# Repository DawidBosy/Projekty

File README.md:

# Projekty
Projekty wykonywane w trakcie studiów

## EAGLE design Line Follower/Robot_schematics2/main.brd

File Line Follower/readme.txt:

Dawid Bosy
Projekt dotyczył przedmiotu Architektura Systemów Komputerowych - wykonywany był na 4 semestrze.
Celem było zbudowanie od podstaw robota, jeżdżącego po zaznaczonej na ziemi linii.

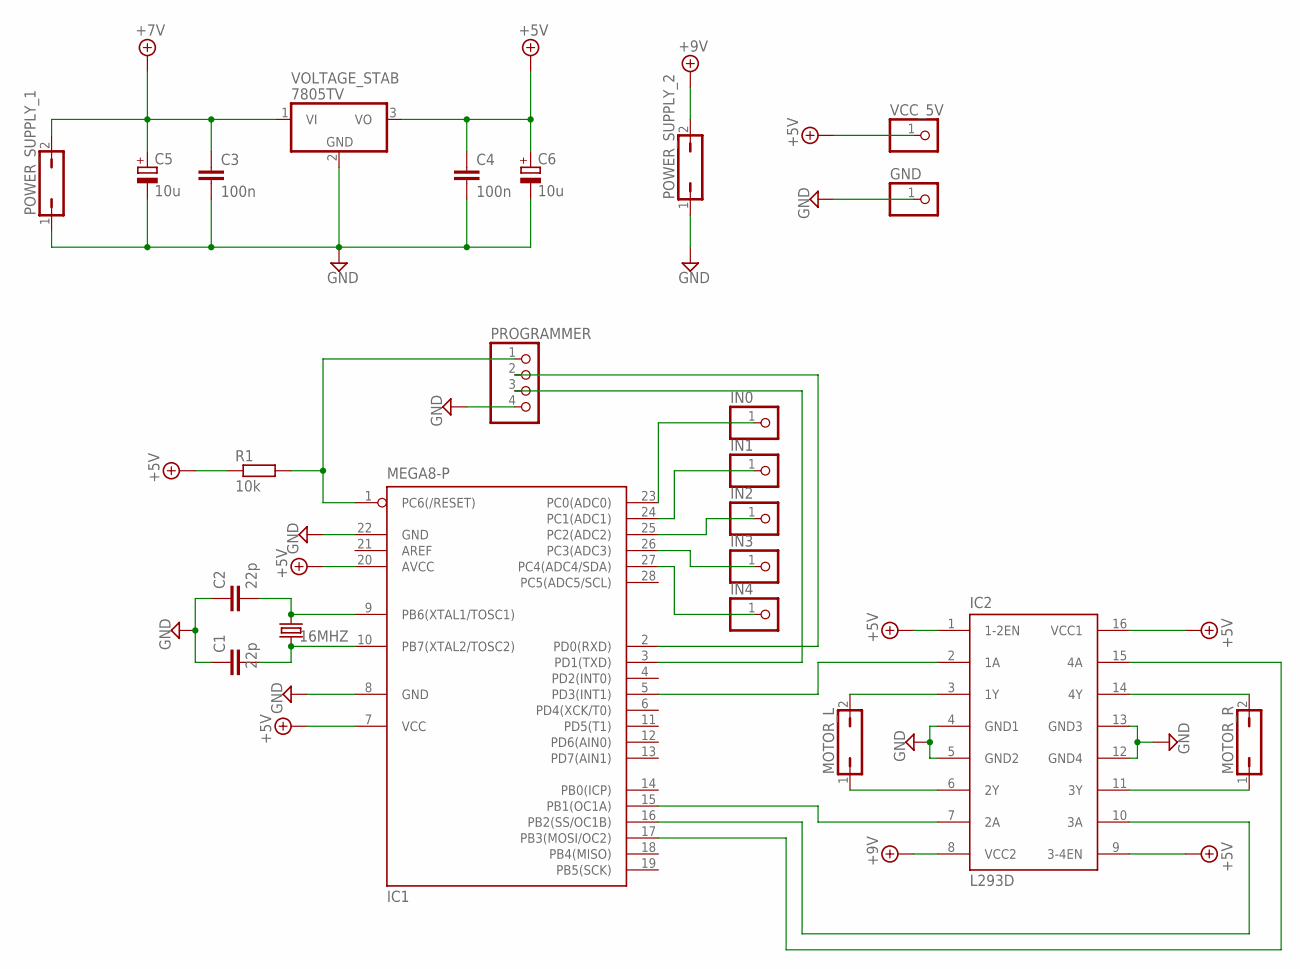
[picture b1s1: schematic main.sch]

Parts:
16MHZ: CRYSTALHC49S; HC49/S
C1, C2: 22p; C025-030X050
C3, C4: 100n; C025-030X050
C5, C6: 10u; E2,5-7
GND: PINHD-1X1; 1X01
IC1: MEGA8-P; DIL28-3
IC2: L293D; DIL16
IN0, IN1, IN2, IN3, IN4: PINHD-1X1; 1X01
MOTOR_L: JP1Q; JP1
MOTOR_R: JP1Q; JP1
POWER_SUPPLY_1, POWER_SUPPLY_2: JP1Q; JP1
PROGRAMMER: PINHD-1X4; 1X04
R1: 10k; 0204/5
VCC_5V: PINHD-1X1; 1X01
VOLTAGE_STAB: 7805TV; TO220V

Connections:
+5V: C4.1, C6.+, IC1.7 (VCC), IC1.20 (AVCC), IC2.1 (1-2EN), IC2.9 (3-4EN), IC2.16 (VCC1), R1.1, VCC_5V.1, VOLTAGE_STAB.3 (VO)
+7V: C3.1, C5.+, POWER_SUPPLY_1.2, VOLTAGE_STAB.1 (VI)
+9V: IC2.8 (VCC2), POWER_SUPPLY_2.2
GND: C1.1, C2.1, C3.2, C4.2, C5.-, C6.-, GND.1, IC1.8 (GND), IC1.22 (GND), IC2.4 (GND1), IC2.5 (GND2), IC2.12 (GND4), IC2.13 (GND3), POWER_SUPPLY_1.1, POWER_SUPPLY_2.1, PROGRAMMER.4, VOLTAGE_STAB.2 (GND)
MOTOR_L_1: IC1.5 (PD3(INT1)), IC2.2 (1A)
MOTOR_L_2: IC1.15 (PB1(OC1A)), IC2.7 (2A)
MOTOR_R2: IC1.17 (PB3(MOSI/OC2)), IC2.15 (4A)
MOTOR_R_1: IC1.16 (PB2(SS/OC1B)), IC2.10 (3A)
unnamed: IC2.11 (3Y), MOTOR_R.1
unnamed: IC2.14 (4Y), MOTOR_R.2
unnamed: IC2.3 (1Y), MOTOR_L.2
unnamed: IC2.6 (2Y), MOTOR_L.1
unnamed: 16MHZ.2, C2.2, IC1.9 (PB6(XTAL1/TOSC1))
unnamed: 16MHZ.1, C1.2, IC1.10 (PB7(XTAL2/TOSC2))
unnamed: IC1.23 (PC0(ADC0)), IN0.1
unnamed: IC1.24 (PC1(ADC1)), IN1.1
unnamed: IC1.25 (PC2(ADC2)), IN2.1
unnamed: IC1.27 (PC4(ADC4/SDA)), IN4.1
unnamed: IC1.26 (PC3(ADC3)), IN3.1
unnamed: IC1.3 (PD1(TXD)), PROGRAMMER.3
unnamed: IC1.2 (PD0(RXD)), PROGRAMMER.2
RESET: IC1.1 (PC6(/RESET)), PROGRAMMER.1, R1.2

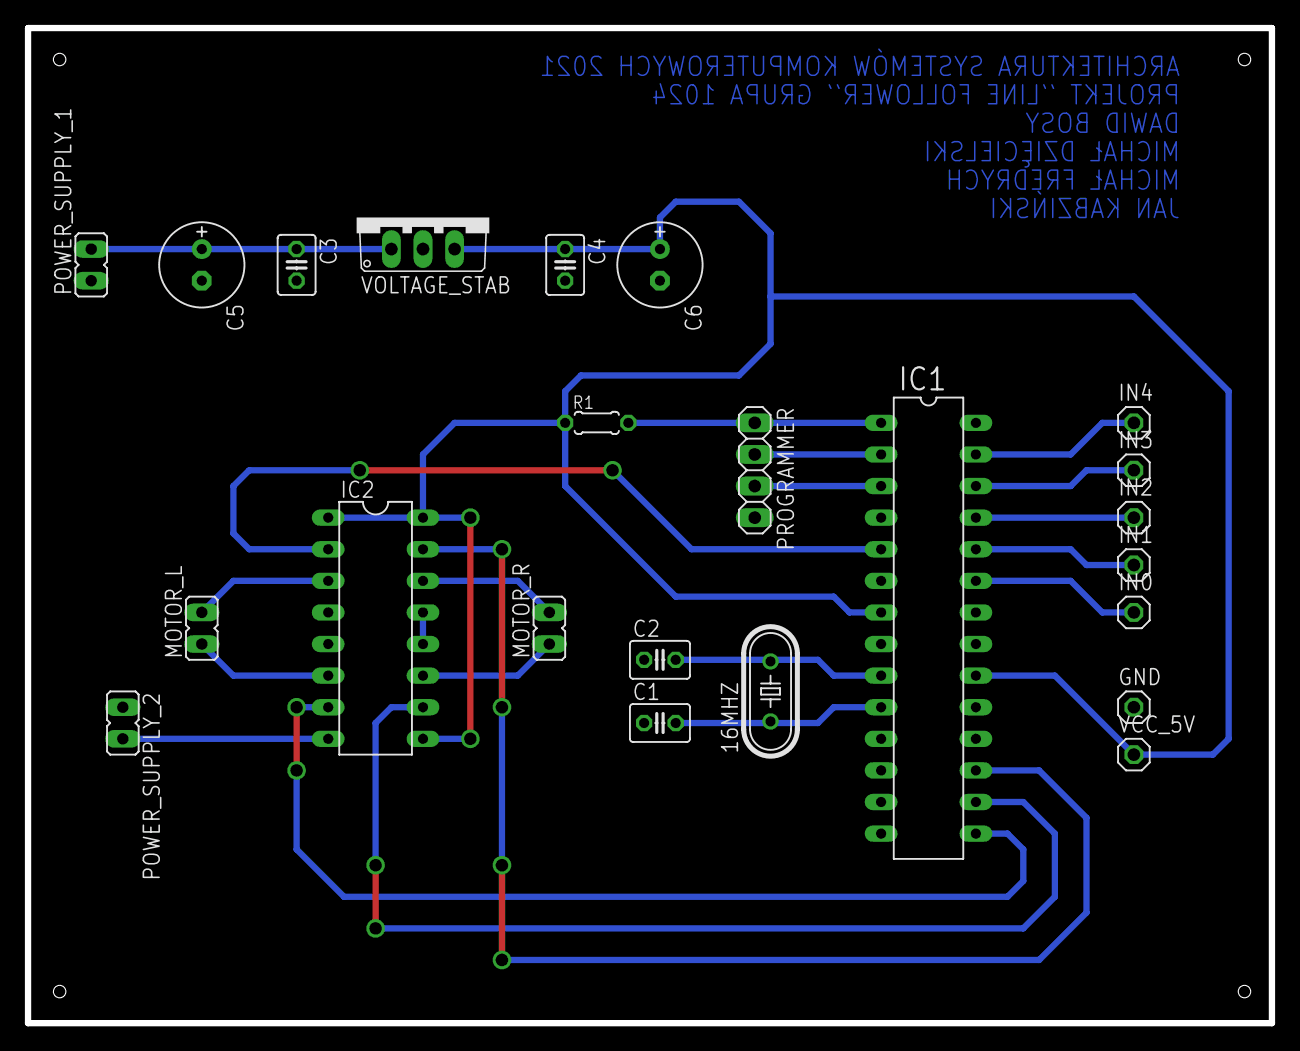
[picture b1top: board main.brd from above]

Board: 2 copper layers, 100.0 x 80.0 mm, 23 parts (0 on the bottom side), 22 nets.

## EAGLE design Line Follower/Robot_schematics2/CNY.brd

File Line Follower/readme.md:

# Robot Line Follower
Projekt dotyczył przedmiotu Architektura Systemów Komputerowych - wykonywany był na 4 semestrze.
Celem było zbudowanie od podstaw robota, jeżdżącego po zaznaczonej na ziemi linii.

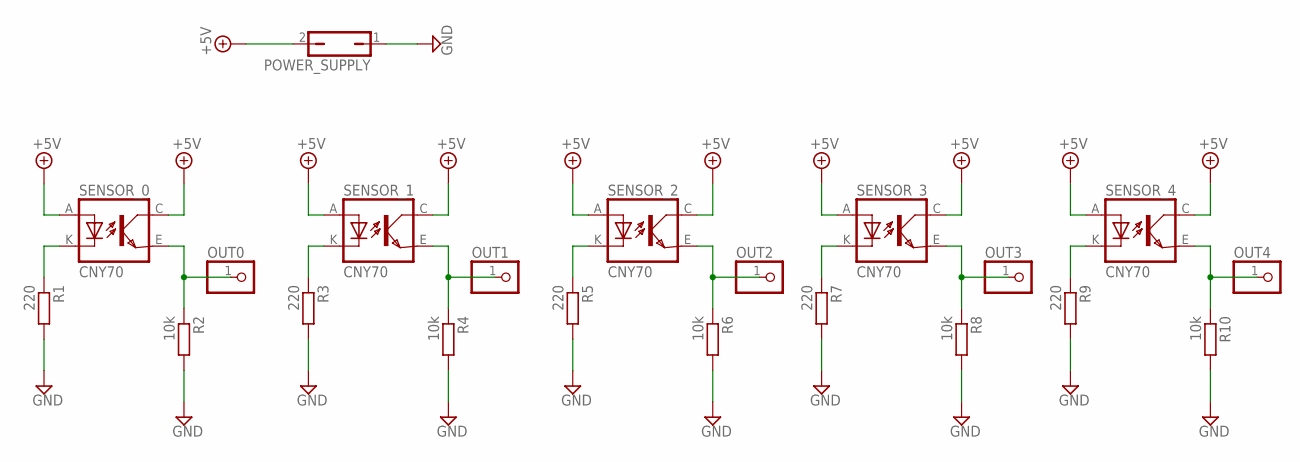
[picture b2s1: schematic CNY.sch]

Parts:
OUT0, OUT1, OUT2, OUT3, OUT4: PINHD-1X1; 1X01
POWER_SUPPLY: JP1Q; JP1
R1, R3, R5, R7, R9: 220; 0204/5
R2, R4, R6, R8, R10: 10k; 0204/5
SENSOR_0, SENSOR_1, SENSOR_2, SENSOR_3, SENSOR_4: CNY70; 4

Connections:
+5V: POWER_SUPPLY.2, SENSOR_0.A, SENSOR_0.C (COL), SENSOR_1.A, SENSOR_1.C (COL), SENSOR_2.A, SENSOR_2.C (COL), SENSOR_3.A, SENSOR_3.C (COL), SENSOR_4.A, SENSOR_4.C (COL)
GND: POWER_SUPPLY.1, R1.2, R2.2, R3.2, R4.2, R5.2, R6.2, R7.2, R8.2, R9.2, R10.2
unnamed: R1.1, SENSOR_0.K (C)
unnamed: R3.1, SENSOR_1.K (C)
unnamed: OUT1.1, R4.1, SENSOR_1.E (EMI)
unnamed: R5.1, SENSOR_2.K (C)
unnamed: OUT2.1, R6.1, SENSOR_2.E (EMI)
unnamed: R7.1, SENSOR_3.K (C)
unnamed: OUT3.1, R8.1, SENSOR_3.E (EMI)
unnamed: R9.1, SENSOR_4.K (C)
unnamed: OUT4.1, R10.1, SENSOR_4.E (EMI)
unnamed: OUT0.1, R2.1, SENSOR_0.E (EMI)

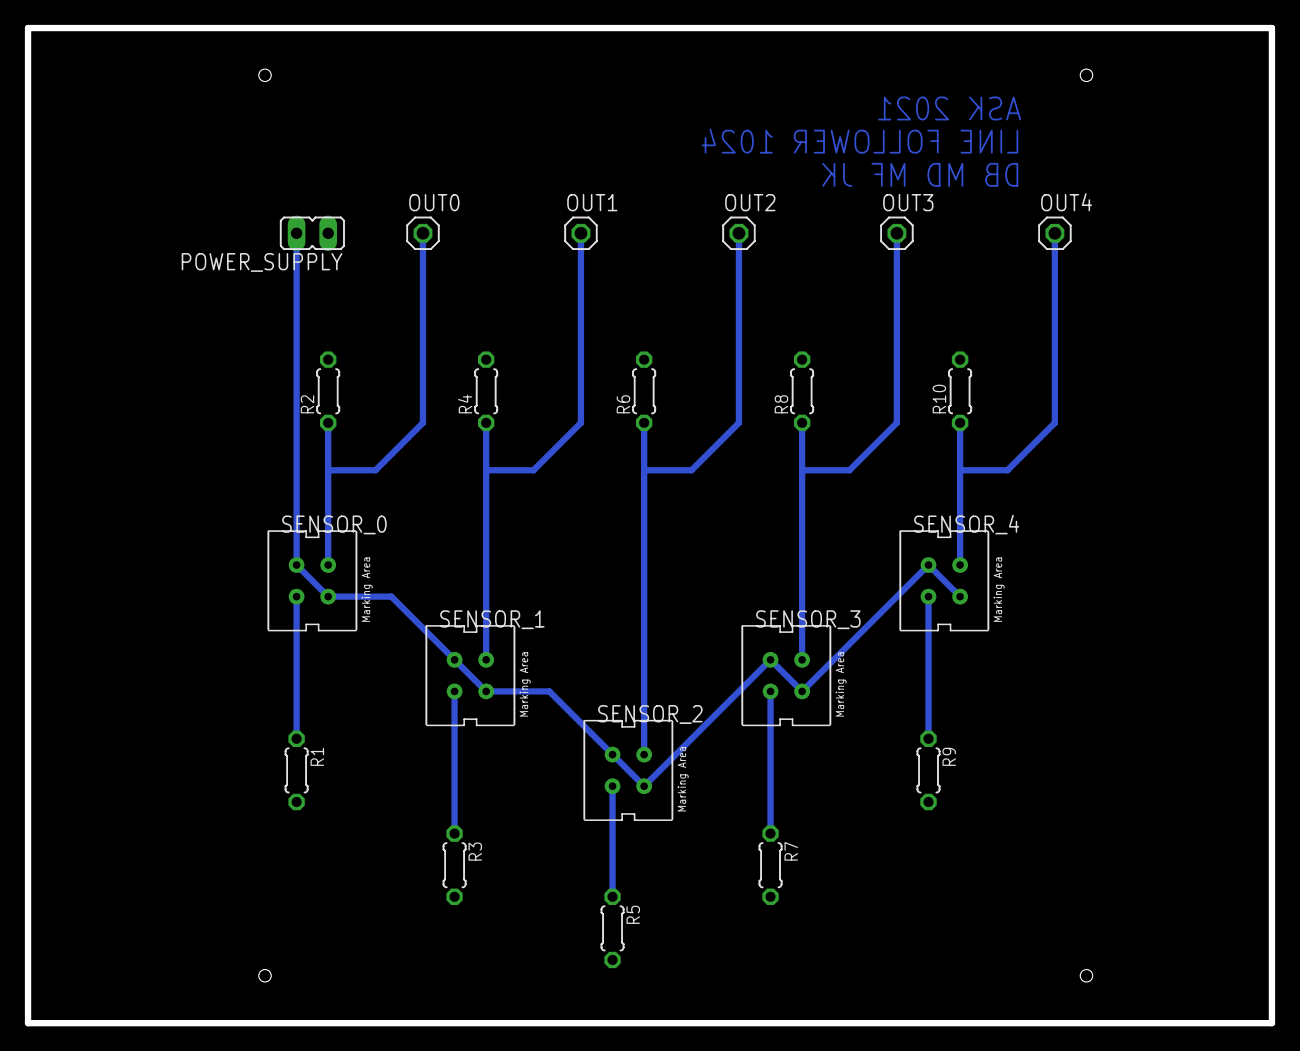
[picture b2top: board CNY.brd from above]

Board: 2 copper layers, 100.0 x 80.0 mm, 21 parts (0 on the bottom side), 12 nets.

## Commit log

2021-12-01 Dodanie projektu dot. Programowania Obiektowego
2021-12-01 Aktualizacja readme
2021-12-01 Dodanie projektu z Podstaw Automatyki
2021-12-01 Dodanie readme
2021-12-01 Dodanie projektu System-Klient
2021-12-01 Dodanie projektu LineFollower
2021-12-01 Dodanie projektu Symulacja Partii Szachowej part 1
2021-12-01 Symulacja Partii Szachowej - part 2
2021-12-01 Symulacja Partii Szachowej - part 3
2021-12-01 Symulacja Partii Szachowej - part 4
2021-12-01 glm2
2021-12-01 glm3
2021-12-01 ext1
2021-12-01 ext2
2021-12-01 gtx1
2021-12-01 gtx2
2021-12-01 Analiza Danych
2022-02-28 Adding Voice Recognition Project
2022-02-28 Adding Card Recognition Project
2022-02-28 Adding first part of 'Space Invaders' Project
2022-02-28 Adding Run App Project
2022-02-28 Added online checkers
2022-02-28 Rename readme.txt to readme.md
2022-02-28 Adding main project files
